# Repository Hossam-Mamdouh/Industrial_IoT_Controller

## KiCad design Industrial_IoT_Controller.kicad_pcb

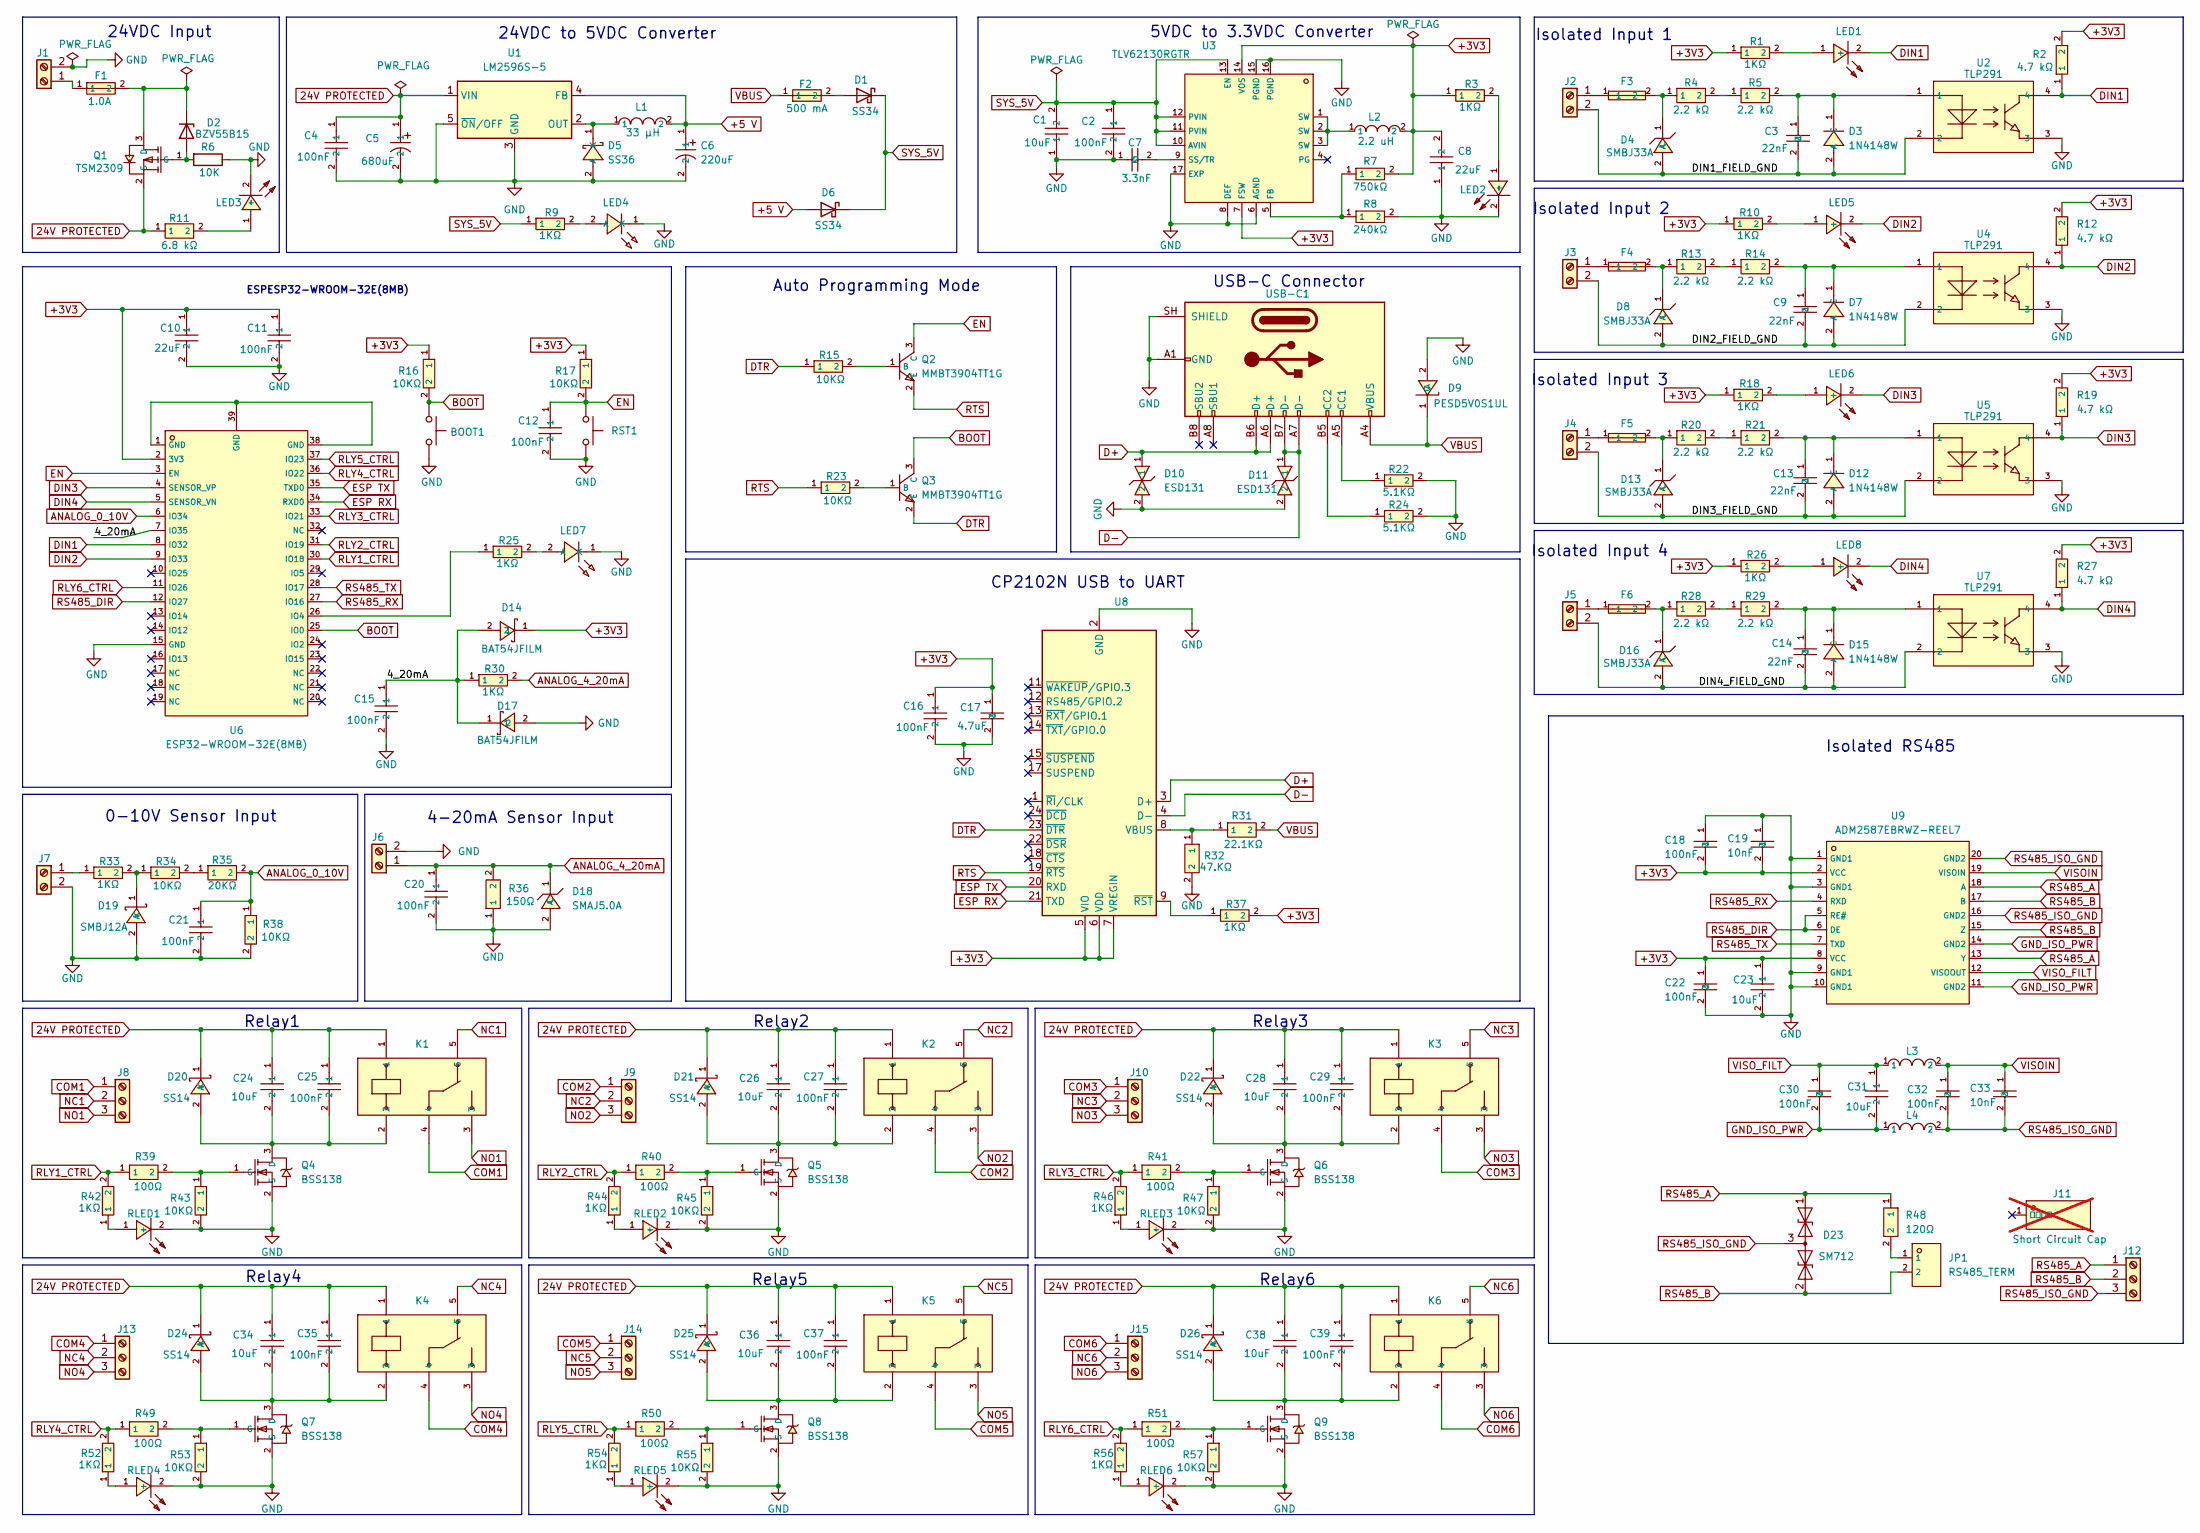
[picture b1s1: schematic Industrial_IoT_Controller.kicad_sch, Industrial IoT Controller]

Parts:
BOOT1: BOOT; SW_PUSH_6mm
C1: 10uF; C15850_C0805; LCSC C15850
C2, C4, C11, C12, C15, C16, C20, C21, C25, C27, C29, C35, C37, C39: 100nF; C1591_C0603; LCSC C1591
C3, C9, C13, C14: 22nF; C1729_C0805; LCSC C1729
C5: 680uF; C48935384_CAP-TH_BD13_0-P5_00-D0_6-FD; LCSC C48935384
C6: 220uF; C2887273_CAP-SMD_BD6_3-L6_6-W6_6-FD; LCSC C2887273
C7: 3.3nF; C77036_C0603; LCSC C77036
C8, C10: 22uF; C907991_C0805; LCSC C907991
C17: 4.7uF; C1779_C0805; LCSC C1779
C18, C22, C30, C32: 100nF; C1590_C0603; LCSC C1590
C19, C33: 10nF; C100042_C0603; LCSC C100042
C23, C31: 10uF; C85713_C0603; LCSC C85713
C24, C26, C28, C34, C36, C38: 10uF; C440198_C0805; LCSC C440198
D1, D6: SS34; D_SMA
D2: BZV55B15; D_MiniMELF
D3, D7, D12, D15: 1N4148W; C917030_SOD-123_L2_8-W1_8-LS3_7-RD-1; LCSC C917030
D4, D8, D13, D16: SMBJ33A; C353366_SMB_L4_4-W3_6-LS5_3-RD; LCSC C353366
D5: SS36; C2922186_SMA_L4_3-W2_6-LS5_2-RD; LCSC C2922186
D9: PESD5V0S1UL; C85402_SOD-882_L1_0-W0_6-RD; LCSC C85402
D10, D11: ESD131; C2939949_WLL-2-3_L0_6-W0_3-P0_36-BI; LCSC C2939949
D14, D17: BAT54JFILM; C86299_SOD-323_L1_8-W1_3-LS2_5-RD; LCSC C86299
D18: SMAJ5.0A; C83329_SMA_L4_3-W2_6-LS5_2-RD; LCSC C83329
D19: SMBJ12A; C50087775_SMB_L4_6-W3_6-LS5_3-RD; LCSC C50087775
D20, D21, D22, D24, D25, D26: SS14; C2480_SMA_L4_2-W2_6-LS5_0-RD_1; LCSC C2480
D23: SM712; SOT-23
F1: 1.0A; C183160_F1206; LCSC C183160
F2: 500 mA; C163512_F1206; LCSC C163512
F3, F4, F5, F6: SMD0805-010-60V; C6851463_F0805; LCSC C6851463
J1, J2, J3, J4, J5, J6, J7: Screw_Terminal_01x02; TerminalBlock_Phoenix_MKDS-3-2-5.08_1x02_P5.08mm_Horizontal
J8, J9, J10, J12, J13, J14, J15: RLY PIN; TerminalBlock_Phoenix_MKDS-3-3-5.08_1x03_P5.08mm_Horizontal
J11: Short Circuit Cap; C5305_FL_001; LCSC C5305; not fitted
JP1: RS485_TERM; C32713268_HDR-TH_2P-P2_54-V-M-3; LCSC C32713268
K1, K2, K3, K4, K5, K6: JQC-3FF/024-1ZS(551)_C2976878; C2976878_RELAY-TH_HF_JQC-3FF; LCSC C2976878
L1: 33 µH; C177245_IND-SMD_L7_0-W6_6_FXL0630; LCSC C177245
L2: 2.2 uH; C53198556_IND-SMD_L4_1-W4_1_ASFPIG4020; LCSC C53198556
L3, L4: 600Ω±25% @100MHz; C85833_L0603; LCSC C85833
LED1, LED2, LED5, LED6, LED8: 0805; C2296_LED0805-R-RD; LCSC C2296
LED3: YLED0805R; C19171391_LED0805-R-RD_RED; LCSC C19171391
LED4, LED7: XL-2012UBC; C965817_LED0805-RD; LCSC C965817
Q1: TSM2309; C2977534_SOT-23-3_L2_9-W1_6-P1_90-LS2_8-BR; LCSC C2977534
Q2, Q3: MMBT3904TT1G; C242260_SC-75-3_L1_6-W0_8-P1_00-LS1_6-BR; LCSC C242260
Q4, Q5, Q6, Q7, Q8, Q9: BSS138; C52895_SOT-23-3_L2_9-W1_6-P1_90-LS2_8-BR; LCSC C52895
R1, R3, R9, R10, R18, R25, R26, R30, R33, R37, R42, R44, R46, R52, R54, R56: 1KΩ; C22548_R0603; LCSC C22548
R2, R12, R19, R27: 4.7 kΩ; C99782_R0603; LCSC C99782
R4, R5, R13, R14, R20, R21, R28, R29: 2.2 kΩ; C525570_R1206; LCSC C525570
R6: 10K; R_0805_2012Metric
R7: 750kΩ; C137684_R0603; LCSC C137684
R8: 240kΩ; C137765_R0603; LCSC C137765
R11: 6.8 kΩ; C54102246_R1206; LCSC C54102246
R15, R16, R17, R23, R34, R38, R43, R45, R47, R53, R55, R57: 10KΩ; C98220_R0603; LCSC C98220
R22, R24: 5.1KΩ; C25905_R0402; LCSC C25905
R31: 22.1KΩ; C2960862_R0603; LCSC C2960862
R32: 47.KΩ; C403243_R0603; LCSC C403243
R35: 20KΩ; C2907011_R0603; LCSC C2907011
R36: 150Ω; C7065937_R0805; LCSC C7065937
R39, R40, R41, R49, R50, R51: 100Ω; C2906981_R0603; LCSC C2906981
R48: 120Ω; C125925_R0603; LCSC C125925
RLED1, RLED2, RLED3, RLED4, RLED5, RLED6: 0805; C2296_LED0805-R-RD; LCSC C2296
RST1: RESET; SW_PUSH_6mm
U1: LM2596S-5; TO-263-5_TabPin3
U2, U4, U5, U7: TLP291; C55144_SOP-4_L4_4-W2_8-P1_27-LS7_0-BR; LCSC C55144
U3: TLV62130RGTR; C122479_QFN-16_L3_0-W3_0-P0_50-TL-EP; LCSC C122479
U6: ESP32-WROOM-32E(8MB); C701342_WIFI-SMD_ESP32-WROOM-32E; LCSC C701342
U8: CP2102N-Axx-xQFN24; QFN-24-1EP_4x4mm_P0.5mm_EP2.6x2.6mm
U9: ADM2587EBRWZ-REEL7; C12081_SOIC-20_L13_0-W7_6-P1_27-LS10_3-BL; LCSC C12081
USB-C1: USB_C_Receptacle_USB2.0_16P; USB_C_Receptacle_HRO_TYPE-C-31-M-12

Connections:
24V PROTECTED: C4.1, C5.1, C24.1, C25.1, C26.1, C27.1, C28.1, C29.1, C34.1, C35.1, C36.1, C37.1, C38.1, C39.1, D20.1 (K), D21.1 (K), D22.1 (K), D24.1 (K), D25.1 (K), D26.1 (K), K1.1, K2.1, K3.1, K4.1, K5.1, K6.1, Q1.2 (S), R11.1, U1.1 (VIN)
+3V3: C8.2, C10.1, C11.1, C16.1, C17.1, C18.2, C19.2, C22.1, C23.1, D14.1, L2.2, R1.1, R2.2, R3.1, R7.2, R10.1, R12.2, R16.1, R17.1, R18.1, R19.2, R26.1, R27.2, R37.2, U3.7 (FSW), U3.14 (VOS), U6.2 (3V3), U8.5 (VIO), U8.6 (VDD), U8.7 (VREGIN), U9.2 (VCC), U9.8 (VCC)
+5 V: C6.1, D6.2 (A), L1.2, U1.4 (FB)
/4_20mA: C15.1, D14.2, D17.1, R30.1, U6.7 (IO35)
/DIN1_FIELD_GND: C3.2, D3.2 (A), D4.2 (A), J2.2, U2.2
/DIN2_FIELD_GND: C9.2, D7.2 (A), D8.2 (A), J3.2, U4.2
/DIN3_FIELD_GND: C13.2, D12.2 (A), D13.2 (A), J4.2, U5.2
/DIN4_FIELD_GND: C14.2, D15.2 (A), D16.2 (A), J5.2, U7.2
ANALOG_0_10V: C21.1, R35.2, R38.1, U6.6 (IO34)
ANALOG_4_20mA: C20.1, D18.1 (C), J6.1, R30.2, R36.2
BOOT: BOOT1.1, Q3.3 (C), R16.2, U6.25 (IO0)
COM1: J8.1, K1.4
COM2: J9.1, K2.4
COM3: J10.1, K3.4
COM4: J13.1, K4.4
COM5: J14.1, K5.4
COM6: J15.1, K6.4
D+: D10.1, U8.3 (D+), USB-C1.A6 (D+), USB-C1.B6 (D+)
D-: D11.1, U8.4 (D-), USB-C1.A7 (D-), USB-C1.B7 (D-)
DIN1: LED1.2 (-), R2.1, U2.4, U6.8 (IO32)
DIN2: LED5.2 (-), R12.1, U4.4, U6.9 (IO33)
DIN3: LED6.2 (-), R19.1, U5.4, U6.4 (SENSOR_VP)
DIN4: LED8.2 (-), R27.1, U6.5 (SENSOR_VN), U7.4
DTR: Q3.2 (E), R15.1, U8.23 (~DTR)
EN: C12.1, Q2.3 (C), R17.2, RST1.1, U6.3 (EN)
ESP RX: U6.34 (RXD0), U8.21 (TXD)
ESP TX: U6.35 (TXD0), U8.20 (RXD)
GND: BOOT1.2, C1.1, C2.2, C4.2, C5.2, C6.2, C7.1, C8.1, C10.2, C11.2, C12.2, C15.2, C16.2, C17.2, C18.1, C19.1, C20.2, C21.2, C22.2, C23.2, D5.2 (A), D9.2 (A), D10.2, D11.2, D17.2, D18.2 (A), D19.2 (A), J1.2, J6.2, J7.2, LED2.2 (-), LED3.2 (-), LED4.1 (K), LED7.1 (K), Q4.2 (S), Q5.2 (S), Q6.2 (S), Q7.2 (S), Q8.2 (S), Q9.2 (S), R6.1, R8.2, R22.2, R24.2, R32.2, R36.1, R38.2, R43.2, R45.2, R47.2, R53.2, R55.2, R57.2, RLED1.2 (-), RLED2.2 (-), RLED3.2 (-), RLED4.2 (-), RLED5.2 (-), RLED6.2 (-), RST1.2, U1.3 (GND), U1.5 (~ON/OFF), U2.3, U3.6 (AGND), U3.8 (DEF), U3.15 (PGND), U3.16 (PGND), U3.17 (EXP), U4.3, U5.3, U6.15 (GND), U7.3, U8.2 (GND), U8.25 (GND), U9.1 (GND1), U9.3 (GND1), U9.9 (GND1), U9.10 (GND1), USB-C1.A1 (GND), USB-C1.A12 (GND), USB-C1.B1 (GND), USB-C1.B12 (GND), USB-C1.SH (SHIELD)
GND_ISO_PWR: C30.2, C31.2, L4.1, U9.11 (GND2), U9.14 (GND2)
NC1: J8.2, K1.5
NC2: J9.2, K2.5
NC3: J10.2, K3.5
NC4: J13.2, K4.5
NC5: J14.2, K5.5
NC6: J15.2, K6.5
NO1: J8.3, K1.3
NO2: J9.3, K2.3
NO3: J10.3, K3.3
NO4: J13.3, K4.3
NO5: J14.3, K5.3
NO6: J15.3, K6.3
unnamed: D1.2 (A), F2.2
unnamed: D2.2 (A), Q1.1 (G), R6.2
unnamed: D2.1 (K), F1.2, Q1.3 (D)
unnamed: C3.1, D3.1 (C), R5.2, U2.1
unnamed: D4.1 (C), F3.2, R4.1
unnamed: D5.1 (K), L1.1, U1.2 (OUT)
unnamed: C9.1, D7.1 (C), R14.2, U4.1
unnamed: D8.1 (C), F4.2, R13.1
unnamed: C13.1, D12.1 (C), R21.2, U5.1
unnamed: D13.1 (C), F5.2, R20.1
unnamed: C14.1, D15.1 (C), R29.2, U7.1
unnamed: D16.1 (C), F6.2, R28.1
unnamed: D19.1 (K), R33.2, R34.1
unnamed: C24.2, C25.2, D20.2 (A), K1.2, Q4.3 (D)
unnamed: C26.2, C27.2, D21.2 (A), K2.2, Q5.3 (D)
unnamed: C28.2, C29.2, D22.2 (A), K3.2, Q6.3 (D)
unnamed: C34.2, C35.2, D24.2 (A), K4.2, Q7.3 (D)
unnamed: C36.2, C37.2, D25.2 (A), K5.2, Q8.3 (D)
unnamed: C38.2, C39.2, D26.2 (A), K6.2, Q9.3 (D)
unnamed: F1.1, J1.1
unnamed: F3.1, J2.1
unnamed: F4.1, J3.1
unnamed: F5.1, J4.1
unnamed: F6.1, J5.1
unnamed: J7.1, R33.1
unnamed: JP1.1, R48.2
unnamed: L2.1, U3.1 (SW), U3.2 (SW), U3.3 (SW)
unnamed: LED1.1 (+), R1.2
unnamed: LED2.1 (+), R3.2
unnamed: LED3.1 (+), R11.2
unnamed: LED4.2 (A), R9.2
unnamed: LED5.1 (+), R10.2
unnamed: LED6.1 (+), R18.2
unnamed: LED7.2 (A), R25.2
unnamed: LED8.1 (+), R26.2
unnamed: Q2.1 (B), R15.2
unnamed: Q3.1 (B), R23.2
unnamed: Q4.1 (G), R39.2, R43.1
unnamed: Q5.1 (G), R40.2, R45.1
unnamed: Q6.1 (G), R41.2, R47.1
unnamed: Q7.1 (G), R49.2, R53.1
unnamed: Q8.1 (G), R50.2, R55.1
unnamed: Q9.1 (G), R51.2, R57.1
unnamed: R4.2, R5.1
unnamed: R13.2, R14.1
unnamed: R20.2, R21.1
unnamed: R28.2, R29.1
unnamed: R34.2, R35.1
unnamed: R42.1, RLED1.1 (+)
unnamed: R44.1, RLED2.1 (+)
unnamed: R46.1, RLED3.1 (+)
unnamed: R52.1, RLED4.1 (+)
unnamed: R54.1, RLED5.1 (+)
unnamed: R56.1, RLED6.1 (+)
unnamed: R7.1, R8.1, U3.5 (FB)
unnamed: C7.2, U3.9 (SS/TR)
unnamed: U6.1 (GND), U6.38 (GND), U6.39 (GND)
unnamed: R25.1, U6.26 (IO4)
unnamed: R31.1, R32.1, U8.8 (VBUS)
unnamed: R37.1, U8.9 (~RST)
unnamed: R22.1, USB-C1.A5 (CC1)
unnamed: R24.1, USB-C1.B5 (CC2)
RLY1_CTRL: R39.1, R42.2, U6.30 (IO18)
RLY2_CTRL: R40.1, R44.2, U6.31 (IO19)
RLY3_CTRL: R41.1, R46.2, U6.33 (IO21)
RLY4_CTRL: R49.1, R52.2, U6.36 (IO22)
RLY5_CTRL: R50.1, R54.2, U6.37 (IO23)
RLY6_CTRL: R51.1, R56.2, U6.11 (IO26)
RS485_A: D23.1 (A1), J12.1, R48.1, U9.13 (Y), U9.18 (A)
RS485_B: D23.2 (A2), J12.2, JP1.2, U9.15 (Z), U9.17 (B)
RS485_DIR: U6.12 (IO27), U9.5 (RE#), U9.6 (DE)
RS485_ISO_GND: C32.2, C33.2, D23.3 (common), J12.3, L4.2, U9.16 (GND2), U9.20 (GND2)
RS485_RX: U6.27 (IO16), U9.4 (RXD)
RS485_TX: U6.28 (IO17), U9.7 (TXD)
RTS: Q2.2 (E), R23.1, U8.19 (~RTS)
SYS_5V: C1.2, C2.1, D1.1 (K), D6.1 (K), R9.1, U3.10 (AVIN), U3.11 (PVIN), U3.12 (PVIN), U3.13 (EN)
VBUS: D9.1 (C), F2.1, R31.2, USB-C1.A4 (VBUS), USB-C1.A9 (VBUS), USB-C1.B4 (VBUS), USB-C1.B9 (VBUS)
VISOIN: C32.1, C33.1, L3.2, U9.19 (VISOIN)
VISO_FILT: C30.1, C31.1, L3.1, U9.12 (VISOOUT)

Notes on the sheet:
0-10V Sensor Input
Relay3
Isolated Input 3
5VDC to 3.3VDC Converter
ESPESP32-WROOM-32E(8MB)
4-20mA Sensor Input
Isolated Input 4
Isolated RS485
24VDC to 5VDC Converter
Isolated Input 1
Relay5
24VDC Input
USB-C Connector
Relay2
Relay6
CP2102N USB to UART
Relay4
Isolated Input 2
Auto Programming Mode
Relay1

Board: 4 copper layers, 188 parts (11 on the bottom side), 120 nets, no tracks yet.
